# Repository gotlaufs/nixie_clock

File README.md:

# Yet another nixie clock
This is a nixie clock project using some salvaged Russian IN-14 nixie tubes.

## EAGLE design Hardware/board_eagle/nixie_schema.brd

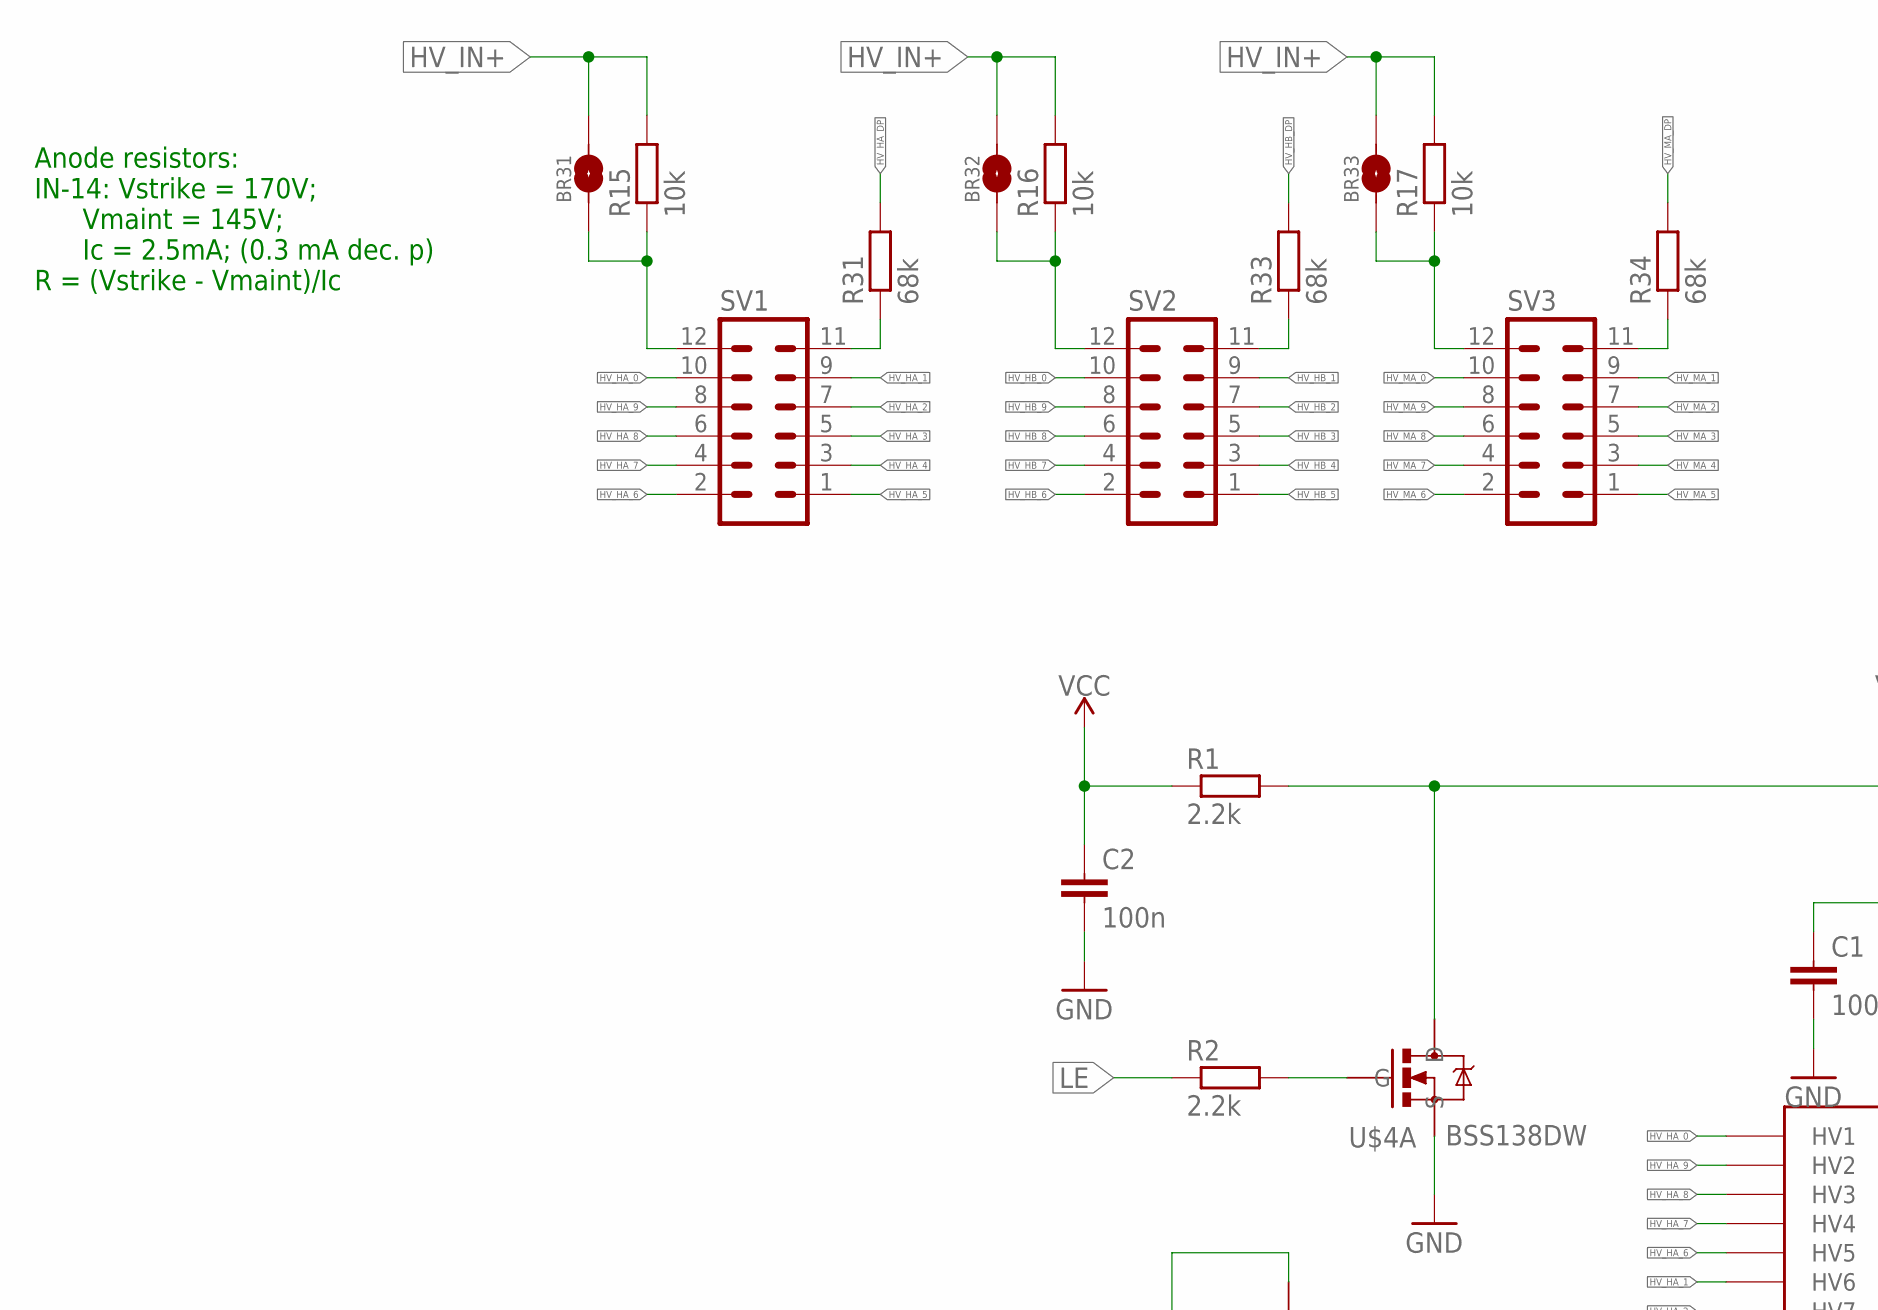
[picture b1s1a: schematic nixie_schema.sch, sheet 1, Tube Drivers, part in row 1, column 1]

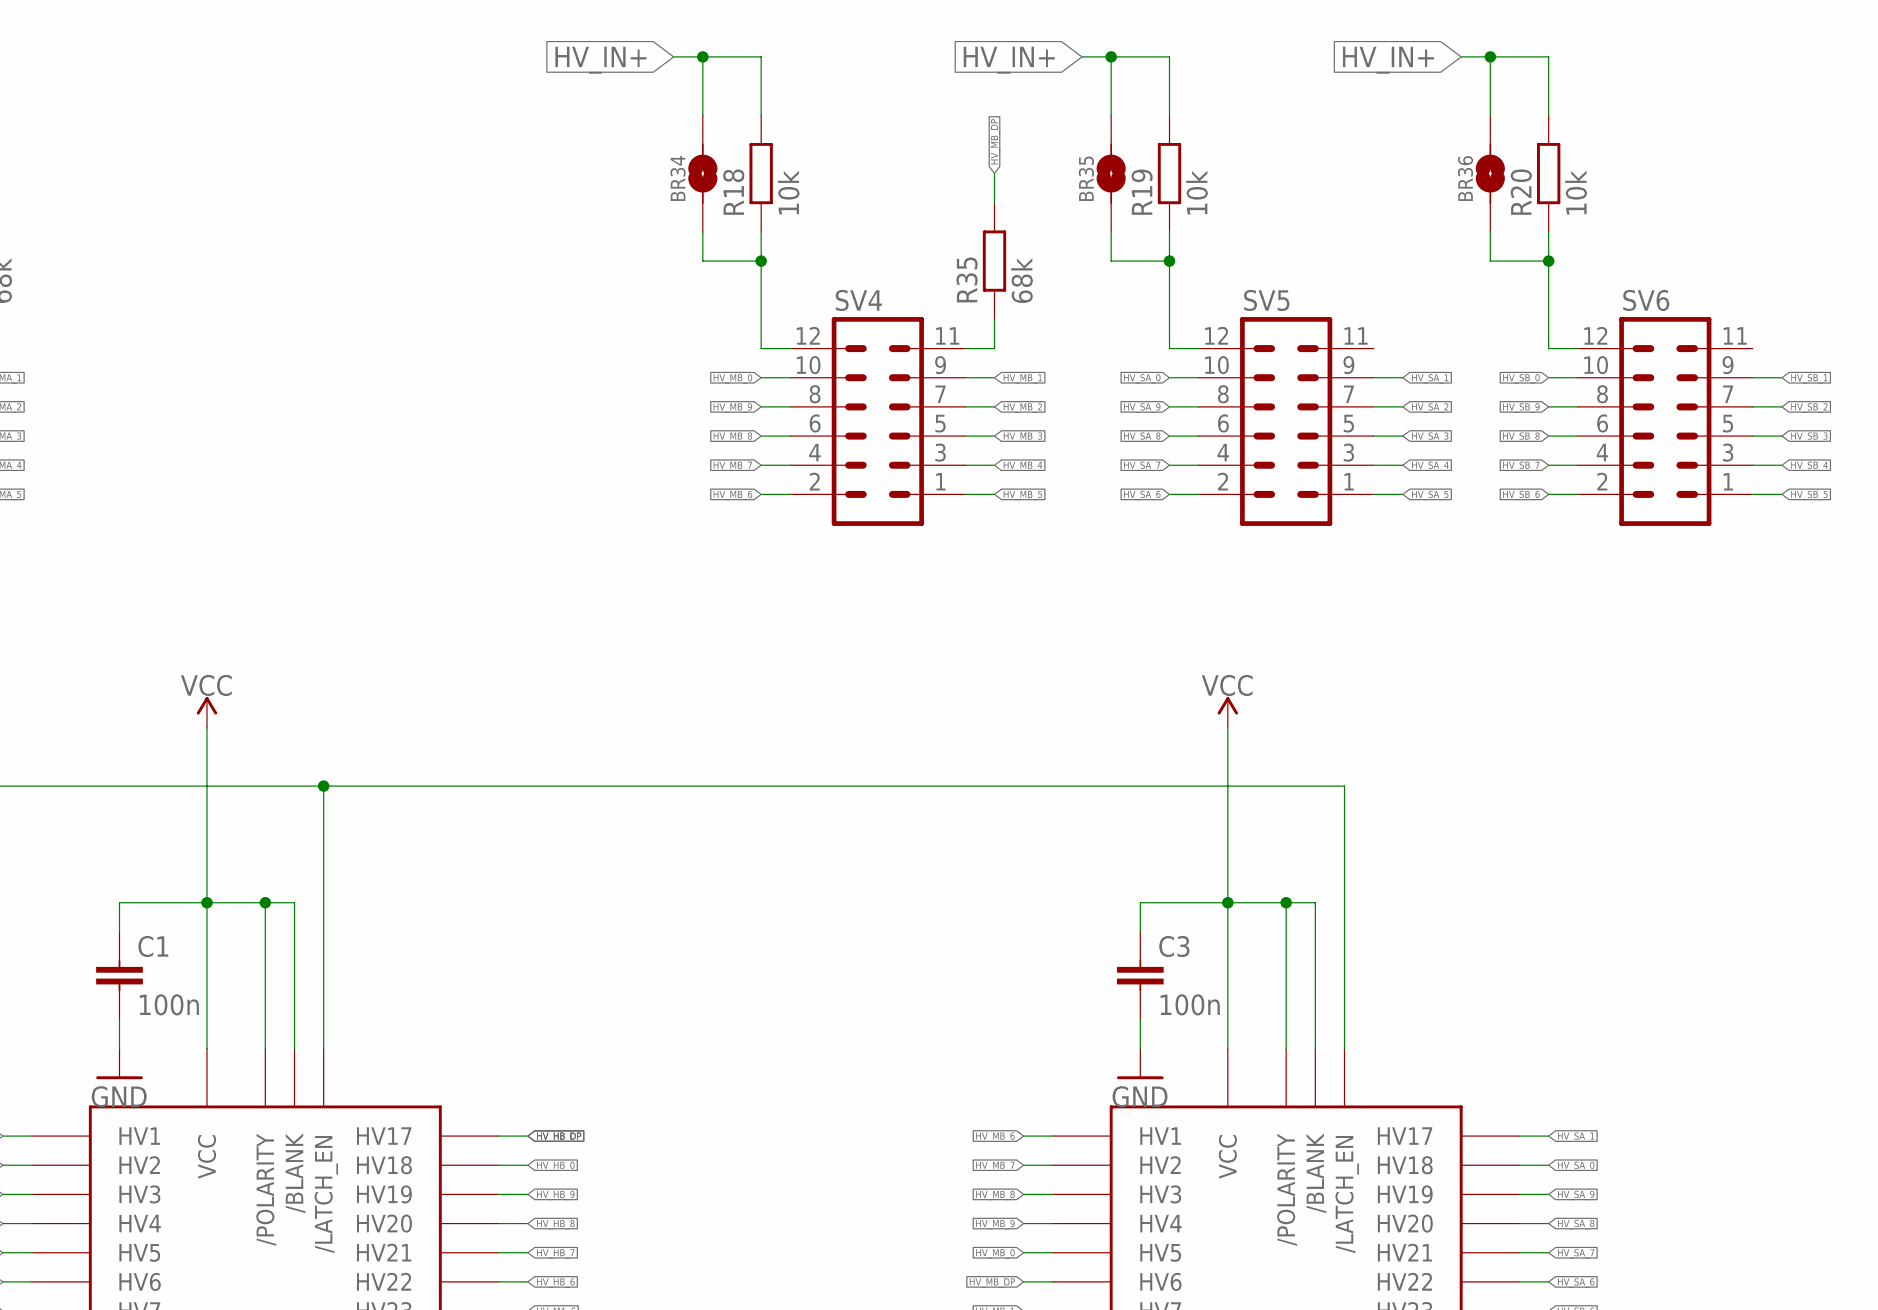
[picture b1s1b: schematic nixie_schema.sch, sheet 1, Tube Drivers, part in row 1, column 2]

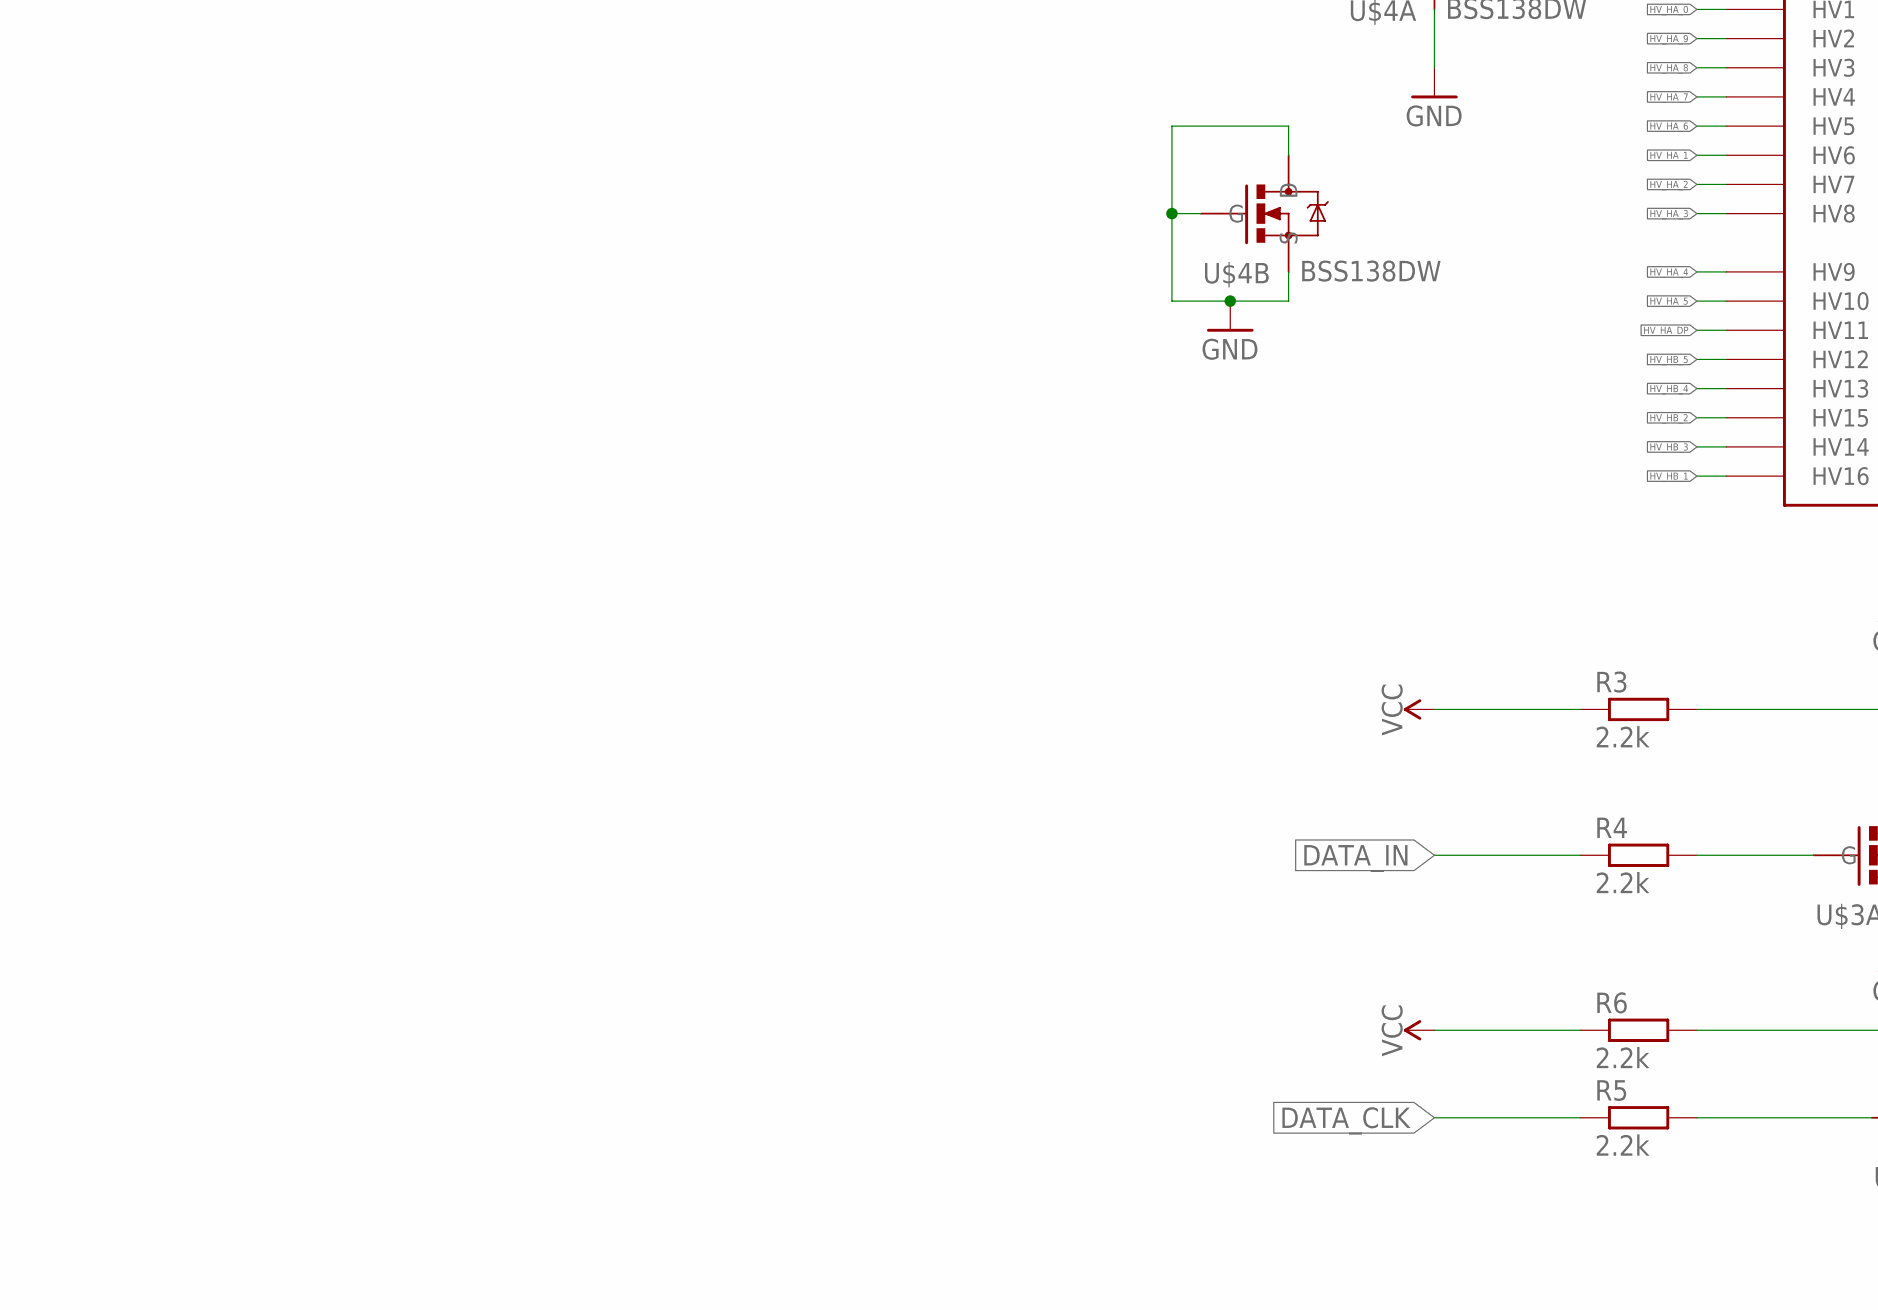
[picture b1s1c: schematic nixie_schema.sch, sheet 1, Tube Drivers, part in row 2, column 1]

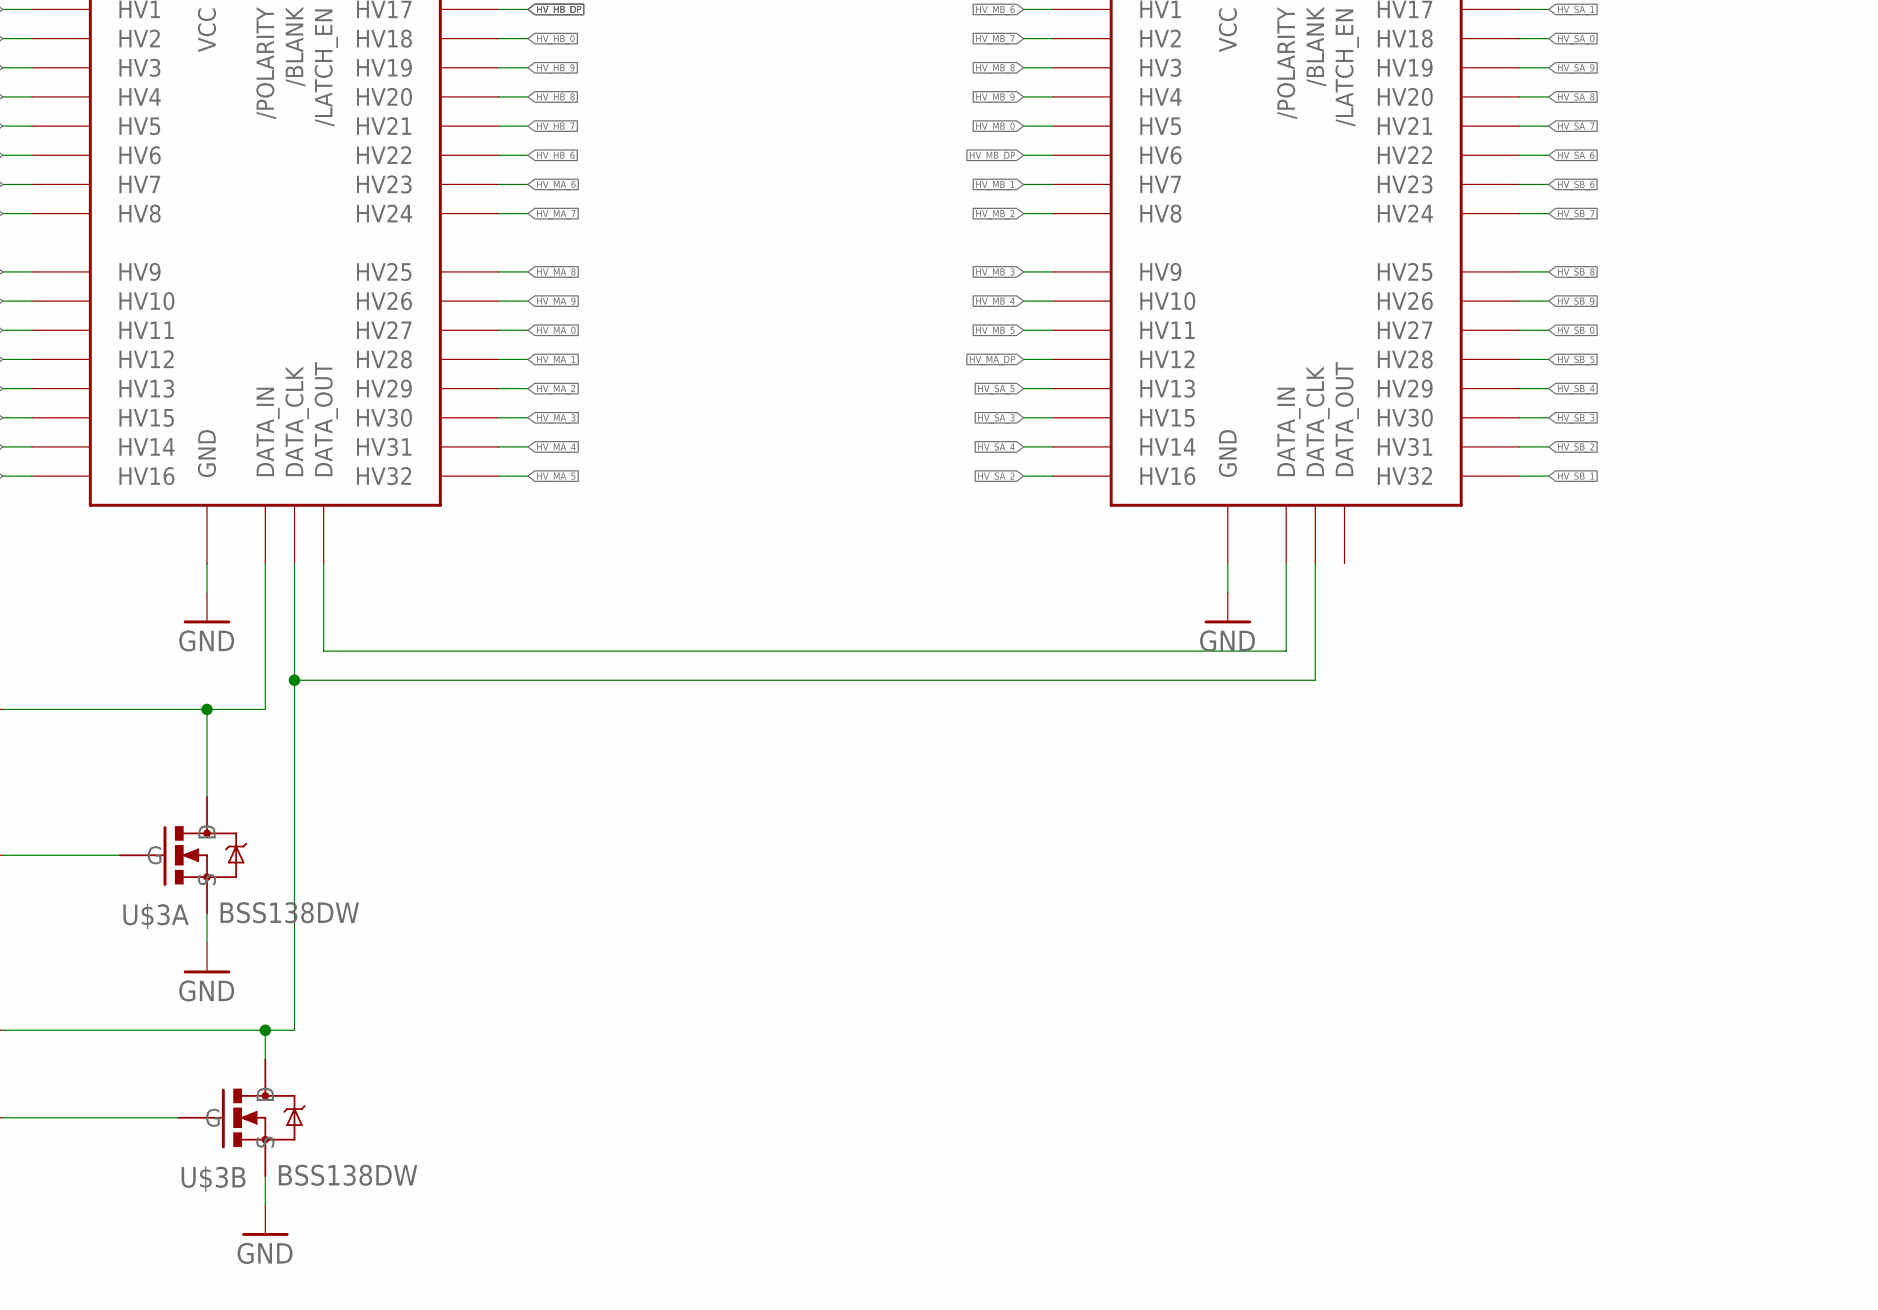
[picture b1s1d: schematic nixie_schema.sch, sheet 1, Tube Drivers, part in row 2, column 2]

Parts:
BR31, BR32, BR33, BR34, BR35, BR36: HV_SOLDER_BRIDGE
C1, C2, C3: 100n; C0805
R1, R2, R3, R4, R5, R6: 2.2k; R0603
R15, R16, R17, R18, R19, R20: 10k; R0603
R31, R33, R34, R35: 68k; R0603
SV1, SV2, SV3, SV4, SV5, SV6: MA06-2
U$1, U$2: HV5522; CQFP-44
U$3, U$4: BSS138DW; SOT-363

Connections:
DATA_CLK: R5.1; also elsewhere on the board
DATA_IN: R4.1; also elsewhere on the board
GND: C1.2, C2.2, C3.2, U$1.24 (GND), U$1.25 (GND), U$1.26 (GND), U$1.29 (GND), U$1.34 (GND), U$2.24 (GND), U$2.25 (GND), U$2.26 (GND), U$2.29 (GND), U$2.34 (GND), U$3.1 (S), U$3.4 (S), U$4.1 (S), U$4.3 (D), U$4.4 (S), U$4.5 (G); also elsewhere on the board
HV_DATA_CLK: R6.2, U$1.28 (DATA_CLK), U$2.28 (DATA_CLK), U$3.3 (D)
HV_DATA_IN: R3.2, U$1.32 (DATA_IN), U$3.6 (D)
HV_DATA_OUT: U$1.23 (DATA_OUT), U$2.32 (DATA_IN)
HV_HA_0: SV1.10, U$1.35 (HV1)
HV_HA_1: SV1.9, U$1.40 (HV6)
HV_HA_2: SV1.7, U$1.41 (HV7)
HV_HA_3: SV1.5, U$1.42 (HV8)
HV_HA_4: SV1.3, U$1.43 (HV9)
HV_HA_5: SV1.1, U$1.44 (HV10)
HV_HA_6: SV1.2, U$1.39 (HV5)
HV_HA_7: SV1.4, U$1.38 (HV4)
HV_HA_8: SV1.6, U$1.37 (HV3)
HV_HA_9: SV1.8, U$1.36 (HV2)
HV_HA_DP: R31.2, U$1.1 (HV11)
HV_HB_0: SV2.10, U$1.8 (HV18)
HV_HB_1: SV2.9, U$1.6 (HV16)
HV_HB_2: SV2.7, U$1.5 (HV15)
HV_HB_3: SV2.5, U$1.4 (HV14)
HV_HB_4: SV2.3, U$1.3 (HV13)
HV_HB_5: SV2.1, U$1.2 (HV12)
HV_HB_6: SV2.2, U$1.12 (HV22)
HV_HB_7: SV2.4, U$1.11 (HV21)
HV_HB_8: SV2.6, U$1.10 (HV20)
HV_HB_9: SV2.8, U$1.9 (HV19)
HV_HB_DP: R33.2, U$1.7 (HV17)
HV_IN+: BR31.P$2 (2), BR32.P$2 (2), BR33.P$2 (2), BR34.P$2 (2), BR35.P$2 (2), BR36.P$2 (2), R15.2, R16.2, R17.2, R18.2, R19.2, R20.2; also elsewhere on the board
HV_LE: R1.2, U$1.31 (/LATCH_EN), U$2.31 (/LATCH_EN), U$4.6 (D)
HV_MA_0: SV3.10, U$1.17 (HV27)
HV_MA_1: SV3.9, U$1.18 (HV28)
HV_MA_2: SV3.7, U$1.19 (HV29)
HV_MA_3: SV3.5, U$1.20 (HV30)
HV_MA_4: SV3.3, U$1.21 (HV31)
HV_MA_5: SV3.1, U$1.22 (HV32)
HV_MA_6: SV3.2, U$1.13 (HV23)
HV_MA_7: SV3.4, U$1.14 (HV24)
HV_MA_8: SV3.6, U$1.15 (HV25)
HV_MA_9: SV3.8, U$1.16 (HV26)
HV_MA_DP: R34.2, U$2.2 (HV12)
HV_MB_0: SV4.10, U$2.39 (HV5)
HV_MB_1: SV4.9, U$2.41 (HV7)
HV_MB_2: SV4.7, U$2.42 (HV8)
HV_MB_3: SV4.5, U$2.43 (HV9)
HV_MB_4: SV4.3, U$2.44 (HV10)
HV_MB_5: SV4.1, U$2.1 (HV11)
HV_MB_6: SV4.2, U$2.35 (HV1)
HV_MB_7: SV4.4, U$2.36 (HV2)
HV_MB_8: SV4.6, U$2.37 (HV3)
HV_MB_9: SV4.8, U$2.38 (HV4)
HV_MB_DP: R35.2, U$2.40 (HV6)
HV_SA_0: SV5.10, U$2.8 (HV18)
HV_SA_1: SV5.9, U$2.7 (HV17)
HV_SA_2: SV5.7, U$2.6 (HV16)
HV_SA_3: SV5.5, U$2.5 (HV15)
HV_SA_4: SV5.3, U$2.4 (HV14)
HV_SA_5: SV5.1, U$2.3 (HV13)
HV_SA_6: SV5.2, U$2.12 (HV22)
HV_SA_7: SV5.4, U$2.11 (HV21)
HV_SA_8: SV5.6, U$2.10 (HV20)
HV_SA_9: SV5.8, U$2.9 (HV19)
HV_SB_0: SV6.10, U$2.17 (HV27)
HV_SB_1: SV6.9, U$2.22 (HV32)
HV_SB_2: SV6.7, U$2.21 (HV31)
HV_SB_3: SV6.5, U$2.20 (HV30)
HV_SB_4: SV6.3, U$2.19 (HV29)
HV_SB_5: SV6.1, U$2.18 (HV28)
HV_SB_6: SV6.2, U$2.13 (HV23)
HV_SB_7: SV6.4, U$2.14 (HV24)
HV_SB_8: SV6.6, U$2.15 (HV25)
HV_SB_9: SV6.8, U$2.16 (HV26)
LE: R2.1; also elsewhere on the board
unnamed: R2.2, U$4.2 (G)
unnamed: R4.2, U$3.2 (G)
unnamed: BR34.P$1 (1), R18.1, SV4.12
unnamed: R5.2, U$3.5 (G)
unnamed: BR33.P$1 (1), R17.1, SV3.12
unnamed: BR31.P$1 (1), R15.1, SV1.12
unnamed: BR32.P$1 (1), R16.1, SV2.12
unnamed: BR36.P$1 (1), R20.1, SV6.12
unnamed: BR35.P$1 (1), R19.1, SV5.12
unnamed: R31.1, SV1.11
unnamed: R33.1, SV2.11
unnamed: R34.1, SV3.11
unnamed: R35.1, SV4.11
VCC: C1.1, C2.1, C3.1, R1.1, R3.1, R6.1, U$1.27 (/POLARITY), U$1.30 (VCC), U$1.33 (/BLANK), U$2.27 (/POLARITY), U$2.30 (VCC), U$2.33 (/BLANK); also elsewhere on the board

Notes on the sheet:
Anode resistors: IN-14: Vstrike = 170V; Vmaint = 145V; Ic = 2.5mA; (0.3 mA dec. p) R = (Vstrike - Vmaint)/Ic

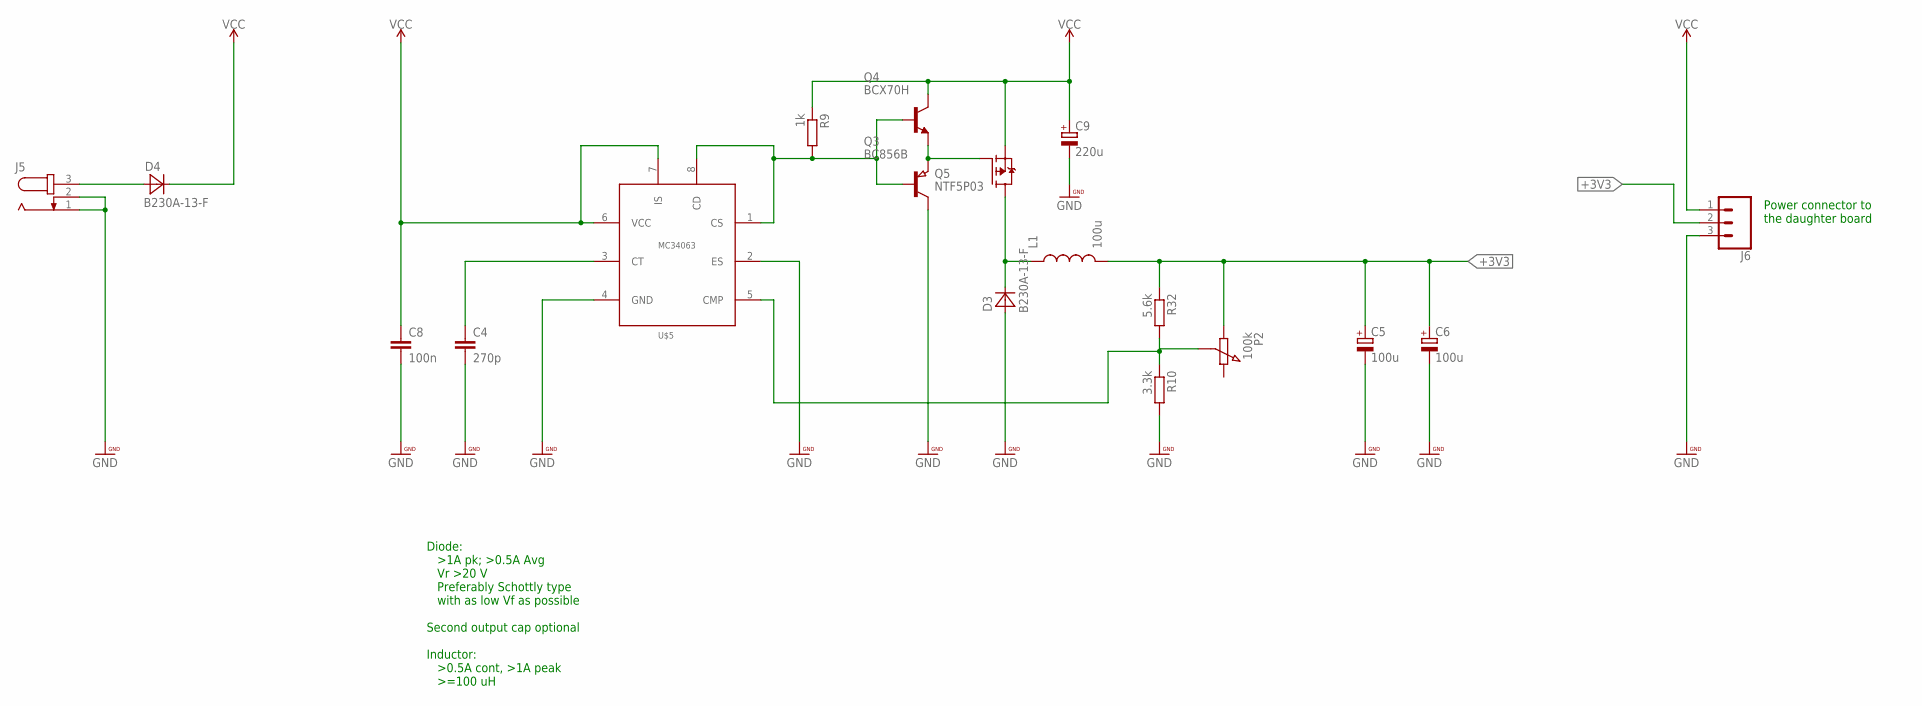
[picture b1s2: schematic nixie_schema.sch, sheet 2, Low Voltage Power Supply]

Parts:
C4: 270p; C0805
C5, C6: 100u; 153CLV-1014
C8: 100n; C0805
C9: 220u; 153CLV-1014
D3, D4: B230A-13-F; SMA/SMB
J5: JACK-PLUG0; SPC4077
J6: CONN_03; 1X03
L1: 100u; INDUCTOR_PACKAGE
P2: 100k; UNI_POT_SMD
Q3: BC856B; SOT23
Q4: BCX70H; SOT23
Q5: NTF5P03; SOT223
R9: 1k; R0603
R10: 3.3k; R0603
R32: 5.6k; R0603
U$5: MC34063; SOIC08

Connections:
+3V3: C5.+, C6.+, J6.2, L1.P$2 (2), P2.P$1 (A), R32.1; also elsewhere on the board
GND: C4.2, C5.-, C6.-, C8.2, C9.-, D3.A, J5.1, J5.2, J6.3, Q3.3 (C), R10.2, U$5.2 (ES), U$5.4 (GND); also elsewhere on the board
unnamed: Q3.1 (B), Q4.1 (B), R9.2, U$5.1 (CS), U$5.8 (CD)
unnamed: C4.1, U$5.3 (CT)
unnamed: D3.C, L1.P$1 (1), Q5.2 (D), Q5.4 (D)
unnamed: D4.A, J5.3
unnamed: Q3.2 (E), Q4.2 (E), Q5.1 (G)
unnamed: P2.P$2 (WIPER), R10.1, R32.2, U$5.5 (CMP)
VCC: C8.1, C9.+, D4.C, J6.1, Q4.3 (C), Q5.3 (S), R9.1, U$5.6 (VCC), U$5.7 (IS); also elsewhere on the board

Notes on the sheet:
Diode: >1A pk; >0.5A Avg Vr >20 V Preferably Schottly type with as low Vf as possible Second output cap optional Inductor: >0.5A cont, >1A peak >=100 uH
Power connector to the daughter board

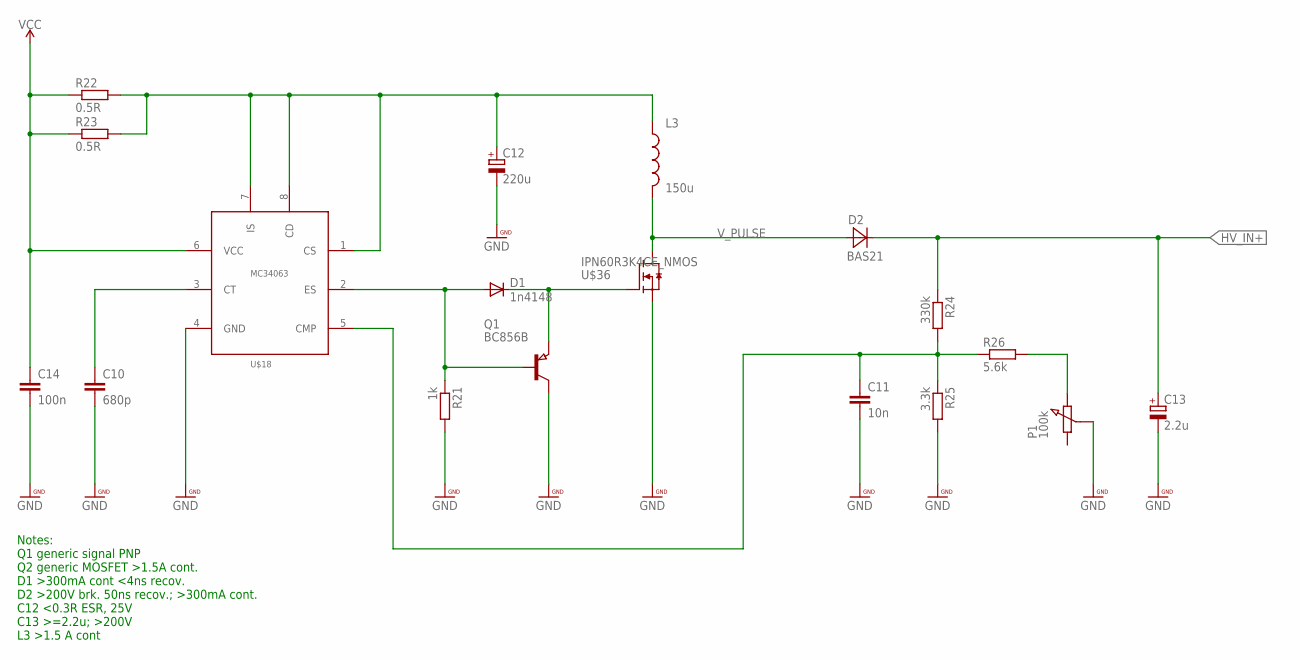
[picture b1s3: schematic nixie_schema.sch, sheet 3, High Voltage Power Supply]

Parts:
C10: 680p; C0805
C11: 10n; C0805
C12: 220u; 153CLV-1014
C13: 2.2u; 153CLV-1014
C14: 100n; C0805
D1: 1n4148; SOD123
D2: BAS21; SOT23
L3: 150u; INDUCTOR_PACKAGE
P1: 100k; UNI_POT_SMD
Q1: BC856B; SOT23
R21: 1k; R0603
R22, R23: 0.5R; R1210
R24: 330k; R0603
R25: 3.3k; R0603
R26: 5.6k; R0603
U$18: MC34063; SOIC08
U$36: IPN60R3K4CE_NMOS; SOT223

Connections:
GND: C10.2, C11.2, C12.-, C13.-, C14.2, P1.P$2 (WIPER), Q1.3 (C), R21.2, R25.2, U$18.4 (GND), U$36.3 (S); also elsewhere on the board
HV_IN+: C13.+, D2.3 (C), R24.1; also elsewhere on the board
unnamed: C10.1, U$18.3 (CT)
unnamed: D1.A, Q1.1 (B), R21.1, U$18.2 (ES)
unnamed: C12.+, L3.P$1 (1), R22.2, R23.2, U$18.1 (CS), U$18.7 (IS), U$18.8 (CD)
unnamed: D1.C, Q1.2 (E), U$36.1 (G)
unnamed: C11.1, R24.2, R25.1, R26.1, U$18.5 (CMP)
unnamed: P1.P$3 (E), R26.2
VCC: C14.1, R22.1, R23.1, U$18.6 (VCC); also elsewhere on the board
V_PULSE: D2.1 (A), L3.P$2 (2), U$36.2 (D), U$36.4 (D)

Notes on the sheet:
Notes: Q1 generic signal PNP Q2 generic MOSFET >1.5A cont. D1 >300mA cont <4ns recov. D2 >200V brk. 50ns recov.; >300mA cont. C12 <0.3R ESR, 25V C13 >=2.2u; >200V L3 >1.5 A cont

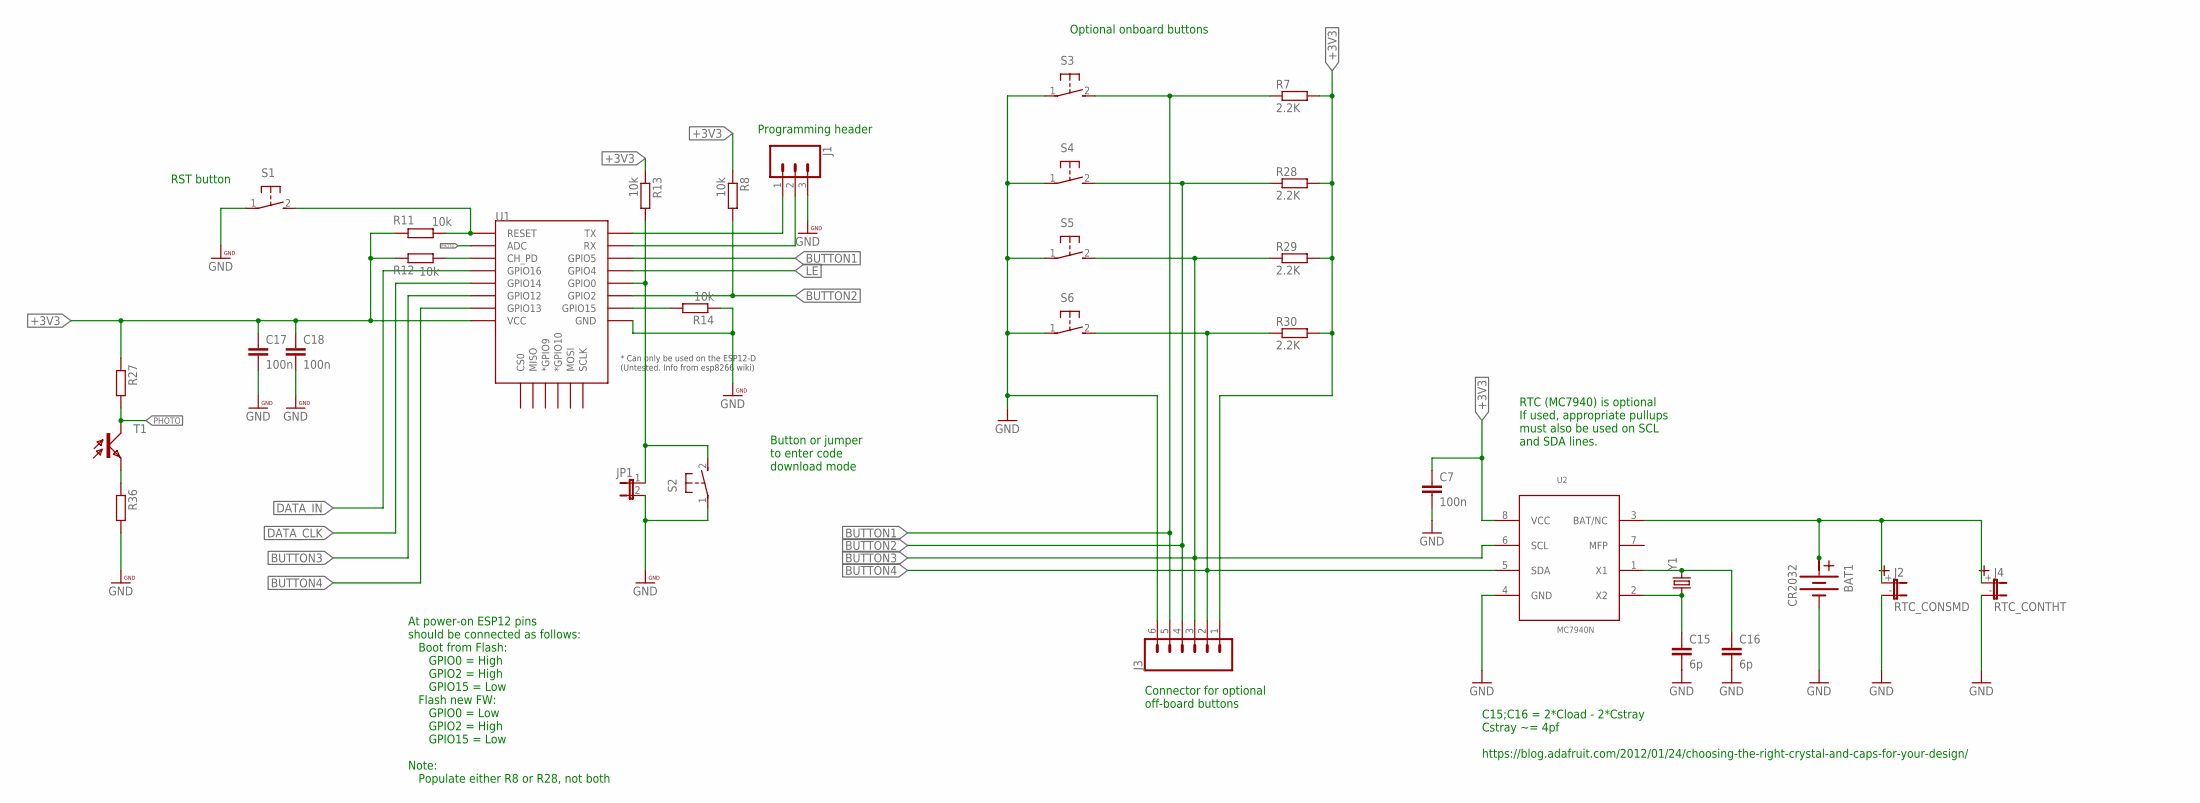
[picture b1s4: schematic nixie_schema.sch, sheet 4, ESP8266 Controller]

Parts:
BAT1: CR2032
C7, C17, C18: 100n; C0805
C15, C16: 6p; C0805
J1: CONN_03; 1X03
J2: RTC_CONSMD; PICOBLADE_SMD_2
J3: CONN_06NO_SILK_FEMALE_PTH; 1X06_NO_SILK
J4: RTC_CONTHT; PICOBLADE_THT_2
JP1: JUMPER2
R7, R28, R29, R30: 2.2K; R0603
R8, R11, R12, R13, R14: 10k; R0603
R27, R36: R-EU_R0603; R0603
S1, S2, S3, S4, S5, S6: 31-XX; B3F-31XX
T1: PHOTO_TRANS; C0805K
U1: ESP12ESMD; ESP12E-SMD
U2: MC7940N; SOIC8-N_MC
Y1: ECS-.327-7-34B; CRYSTAL_PACK

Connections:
+: BAT1.+_2 (+)
+3V3: C7.1, C17.1, C18.1, J3.1, R7.2, R8.1, R11.2, R12.2, R13.1, R27.1, R28.2, R29.2, R30.2, U1.VCC, U2.8 (VCC); also elsewhere on the board
BUTTON1: J3.5, R7.1, S3.2 (S), U1.GPIO5
BUTTON2: J3.4, R8.2, R28.1, S4.2 (S), U1.GPIO2
BUTTON3: J3.3, R29.1, S5.2 (S), U1.GPIO12, U2.6 (SCL)
BUTTON4: J3.2, R30.1, S6.2 (S), U1.GPIO13, U2.5 (SDA)
DATA_CLK: U1.GPIO14; also elsewhere on the board
DATA_IN: U1.GPIO16; also elsewhere on the board
GND: BAT1.-, C7.2, C15.2, C16.2, C17.2, C18.2, J1.3, J2.-, J3.6, J4.-, JP1.2, R14.1, R36.2, S1.1, S2.1, S3.1, S4.1, S5.1, S6.1, U1.GND, U2.4 (GND); also elsewhere on the board
LE: U1.GPIO4; also elsewhere on the board
unnamed: R11.1, S1.2 (S), U1.RESET
unnamed: JP1.1, R13.2, S2.2 (S), U1.GPIO0
unnamed: R12.1, U1.CH_PD
unnamed: J1.1, U1.TXD0 (TX)
unnamed: J1.2, U1.RXD0 (RX)
unnamed: R14.2, U1.GPIO15
unnamed: BAT1.+_1 (+), J2.+, J4.+, U2.3 (BAT/NC)
unnamed: C16.1, U2.1 (X1), Y1.P$2 (2)
unnamed: C15.1, U2.2 (X2), Y1.P$1 (1)
unnamed: R36.1, T1.EMI (E)
PHOTO: R27.2, T1.COL (C), U1.ADC

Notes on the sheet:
RTC (MC7940) is optional If used, appropriate pullups must also be used on SCL and SDA lines.
Programming header
Connector for optional off-board buttons
RST button
Button or jumper to enter code download mode
Optional onboard buttons
At power-on ESP12 pins should be connected as follows: Boot from Flash: GPIO0 = High GPIO2 = High GPIO15 = Low Flash new FW: GPIO0 = Low GPIO2 = High GPIO15 = Low Note: Populate either R8 or R28, not both
C15;C16 = 2*Cload - 2*Cstray Cstray ~= 4pf https://blog.adafruit.com/2012/01/24/choosing-the-right-crystal-and-caps-for-your-design/

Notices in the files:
parts and their libraries:
SparkFun-Connectors: Licensing: Creative Commons ShareAlike 4.0 International - https://creativecommons.org/licenses/by-sa/4.0
PatternAgents-JTAG: License : http://creativecommons.org/licenses/by-sa/4.0
(Creative Commons 4.0)
PatternAgents_RFmodules: (Creative Commons 3.0)
